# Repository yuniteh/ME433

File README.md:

yuni teh
03/28/2017
repo for me433

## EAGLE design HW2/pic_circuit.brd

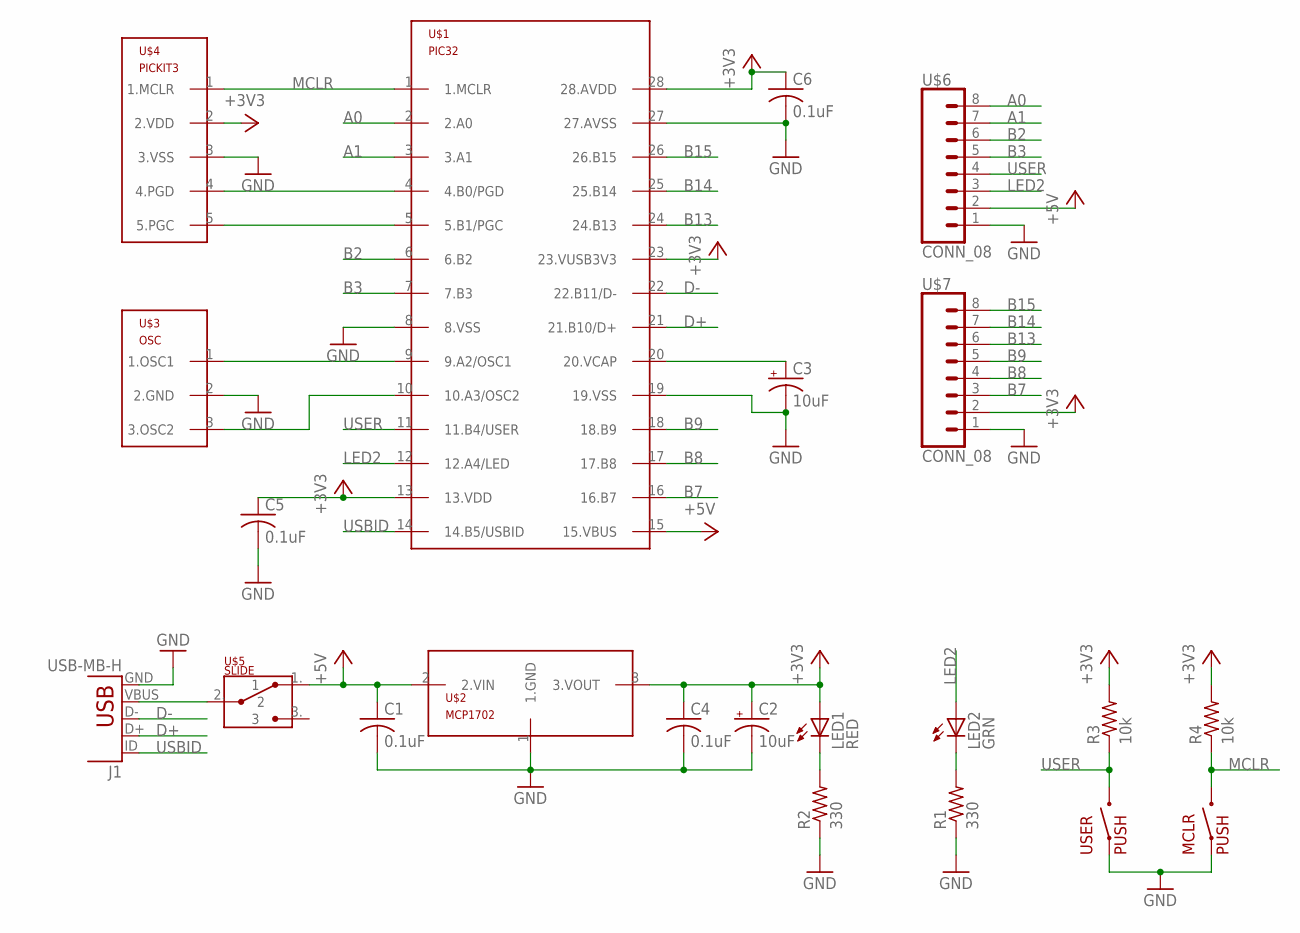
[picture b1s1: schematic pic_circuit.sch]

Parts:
C1, C4, C5, C6: 0.1uF; C025-025X050
C2, C3: 10uF; B45181B
J1: USB-MB-H
LED1: RED; LED3MM
LED2: GRN; LED3MM
MCLR: PUSH; PUSHBUTTON
R1, R2: 330; 0207/10
R3, R4: 10k; 0207/10
U$1: PIC32; DIL28-3
U$2: MCP1702; TO92
U$3: OSC; OSCILLATOR
U$4: PICKIT3; 1X05
U$5: SLIDE; SLIDE-SWITCH
U$6, U$7: CONN_08; 1X08
USER: PUSH; PUSHBUTTON

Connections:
+3V3: C2.+, C4.1, C5.1, C6.1, LED1.A, R3.2, R4.2, U$1.13 (13.VDD), U$1.23 (23.VUSB3V3), U$1.28 (28.AVDD), U$2.3 (3.VOUT), U$4.2 (2.VDD), U$7.2
+5V: C1.1, U$1.15 (15.VBUS), U$2.2 (2.VIN), U$5.1. (1), U$6.2
A0: U$1.2 (2.A0), U$6.8
A1: U$1.3 (3.A1), U$6.7
B2: U$1.6 (6.B2), U$6.6
B3: U$1.7 (7.B3), U$6.5
B7: U$1.16 (16.B7), U$7.3
B8: U$1.17 (17.B8), U$7.4
B9: U$1.18 (18.B9), U$7.5
B13: U$1.24 (24.B13), U$7.6
B14: U$1.25 (25.B14), U$7.7
B15: U$1.26 (26.B15), U$7.8
D+: J1.D+, U$1.21 (21.B10/D+)
D-: J1.D-, U$1.22 (22.B11/D-)
GND: C1.2, C2.-, C3.-, C4.2, C5.2, C6.2, J1.GND, MCLR.1, R1.1, R2.1, U$1.8 (8.VSS), U$1.19 (19.VSS), U$1.27 (27.AVSS), U$2.1 (1.GND), U$3.2 (2.GND), U$4.3 (3.VSS), U$6.1, U$7.1, USER.1
LED2: LED2.A, U$1.12 (12.A4/LED), U$6.3
MCLR: MCLR.2, R4.1, U$1.1 (1.MCLR), U$4.1 (1.MCLR)
unnamed: J1.VBUS, U$5.2. (2)
unnamed: U$1.4 (4.B0/PGD), U$4.4 (4.PGD)
unnamed: LED1.K (C), R2.2
unnamed: U$1.5 (5.B1/PGC), U$4.5 (5.PGC)
unnamed: C3.+, U$1.20 (20.VCAP)
unnamed: U$1.9 (9.A2/OSC1), U$3.1 (1.OSC1)
unnamed: U$1.10 (10.A3/OSC2), U$3.3 (3.OSC2)
unnamed: LED2.K (C), R1.2
USBID: J1.ID, U$1.14 (14.B5/USBID)
USER: R3.1, U$1.11 (11.B4/USER), U$6.4, USER.2

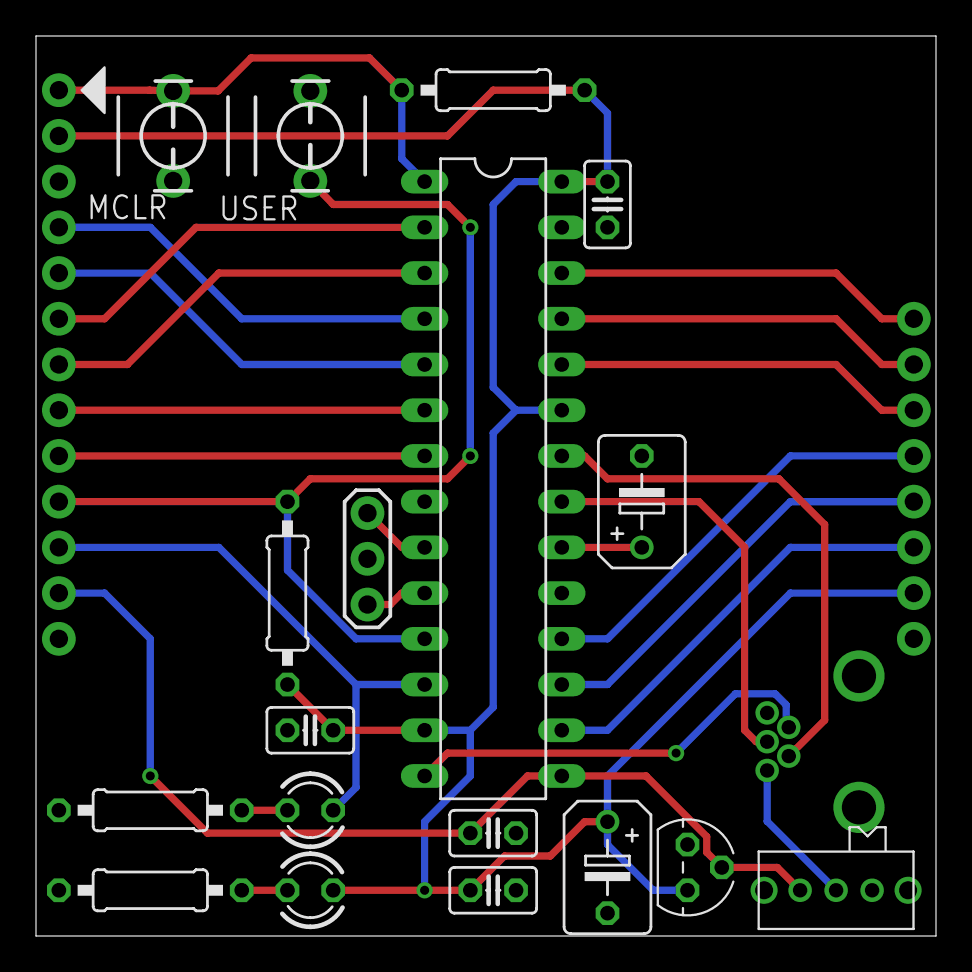
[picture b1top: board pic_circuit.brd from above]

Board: 2 copper layers, 50.0 x 50.0 mm, 22 parts (0 on the bottom side), 27 nets.

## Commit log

2017-03-28 added readme
2017-03-30 edited README
2017-03-30 photo of circuit
2017-03-30 created mplabx project
2017-03-30 edited pragma values
2017-03-30 added TRIS/LAT initializations
2017-03-30 added 1 kHz LED output
2017-03-30 added pushbutton function
2017-03-30 new pic circuit photo
2017-03-30 added demo video
2017-03-30 added voltage regulator screenshots
2017-03-30 added circuit diagram
2017-04-02 edited pic circuit
2017-04-02 created new hw2 eagle project
2017-04-03 completed eagle library
2017-04-03 created pic circuit schematic
2017-04-03 completed schematic
2017-04-03 saved eagle project
2017-04-03 reorganized hw2
2017-04-07 completed pub design
2017-04-07 created hw 3 folder
2017-04-07 zipped gerber files
2017-04-12 initialized spa pins
2017-04-12 added sine and triangle wave outputs to main()
2017-04-12 added oscilloscope screenshot
2017-04-13 edited io_exp library
2017-04-13 write to i2c
2017-04-13 fixed init_exp
2017-04-13 completed hw 5
2017-04-13 added video and circuit diagram
2017-04-18 created LCD_write function
2017-04-18 added write string and bar
2017-04-18 added video
2017-04-21 imu vid
2017-04-27 created harmony project
2017-04-27 added imu video
2017-04-27 created hw 9 project
2017-05-02 print imu but not lcd
2017-05-02 swapped check timer location
2017-05-15 finished hw 9
2017-05-15 uploaded hw9 video
2017-05-15 started hw10
2017-05-16 started hw12
2017-05-18 completed hw12
2017-05-18 completed hw13
2017-05-19 hw14 pre-android
2017-05-19 completed hw14
2017-05-19 fixed IMU bug
2017-05-19 completed maf code
2017-05-19 completed hw11
2017-05-19 edit dip
2017-06-06 added hwk videos
2017-06-06 finished box cad
2017-06-07 image processing app
2017-06-07 completed hw 19
2017-06-07 cad stuff
2017-06-07 wheel photos
2017-06-07 edited motor control
2017-06-08 box photo
2017-06-09 added motor video
2017-06-09 android usb camera merge
2017-06-09 finished hw20
2017-06-09 final video
2019-11-10 testing terminal
2019-11-10 test github
